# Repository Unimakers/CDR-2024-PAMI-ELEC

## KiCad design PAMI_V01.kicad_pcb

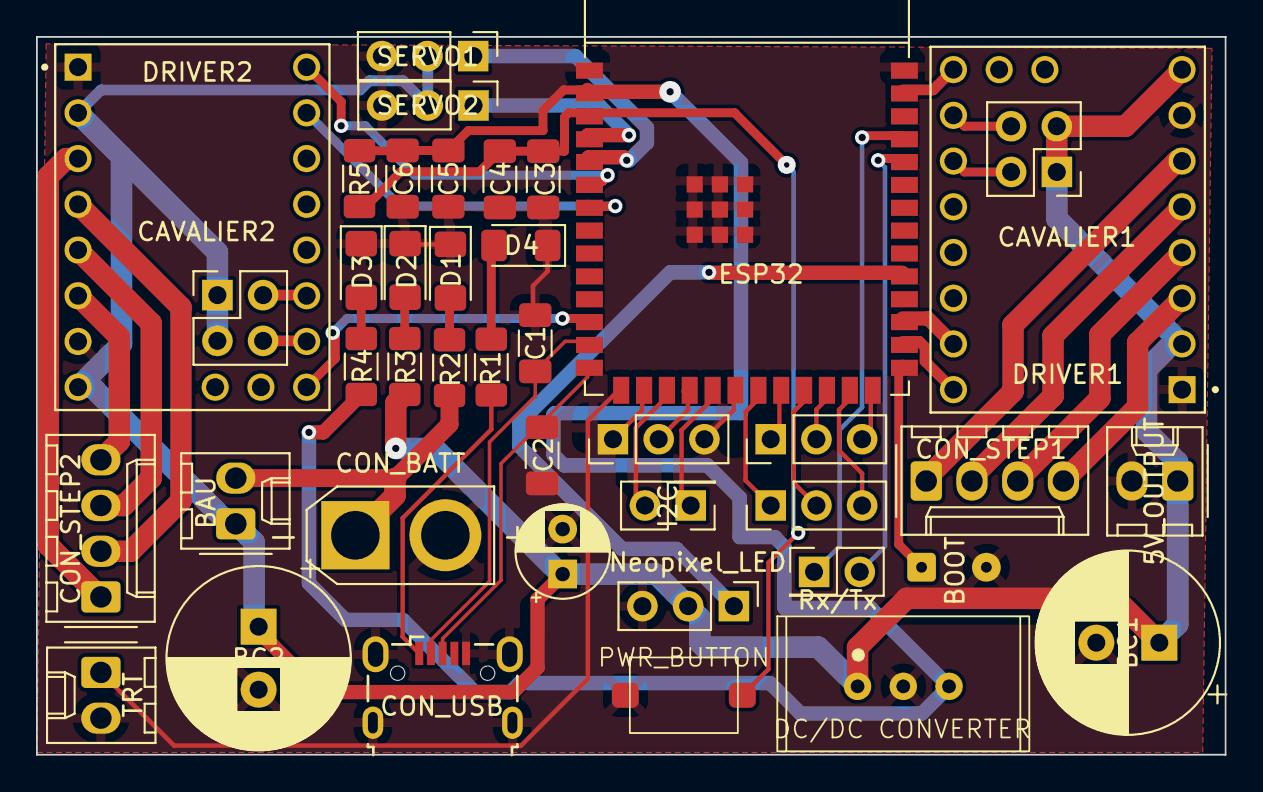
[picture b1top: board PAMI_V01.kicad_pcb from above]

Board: 2 copper layers, 66.0 x 39.9 mm, 41 parts (0 on the bottom side), 48 nets.

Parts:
5V_OUTPUT: Conn; Molex_KK-254_AE-6410-02A_1x02_P2.54mm_Vertical
BAU: BAU; Molex_KK-254_AE-6410-02A_1x02_P2.54mm_Vertical
BC1, BC2: 100uF; CP_Radial_D10.0mm_P3.50mm
BOOT: Conn; SolderWire-0.1sqmm_1x02_P3.6mm_D0.4mm_OD1mm
C1, C2, C4: TBD; C_1206_3216Metric_Pad1.33x1.80mm_HandSolder
C3, C5: 0.1uF; C_1206_3216Metric_Pad1.33x1.80mm_HandSolder
C6: 22uF; C_1206_3216Metric_Pad1.33x1.80mm_HandSolder
C7: 10uF; CP_Radial_D5.0mm_P2.50mm
CAVALIER1, CAVALIER2: Conn_02x02_Odd_Even; PinHeader_2x02_P2.54mm_Vertical
CON_BATT: Conn; AMASS_XT30U-F_1x02_P5.0mm_Vertical
CON_STEP1, CON_STEP2: Conn_01x04; Molex_KK-254_AE-6410-04A_1x04_P2.54mm_Vertical
CON_USB: USB_OTG; USB_Micro-B_Wuerth_629105150521
D1, D2, D3, D4: LED_Small; LED_1206_3216Metric_Pad1.42x1.75mm_HandSolder
DC/DC CONVERTER: TSR_2-2433; Traco 2- 24xx
DRIVER1, DRIVER2: TMC2209_SILENTSTEPSTICK; MODULE_TMC2209_SILENTSTEPSTICK
ESP32: ESP32-S3-WROOM-1
I2C: Conn_01x02; PinHeader_2x01_P2.54mm_Vertical
J7, J9, J11: Conn_01x03; PinHeader_1x03_P2.54mm_Vertical
Neopixel_LED: Neopixel_LED; PinHeader_1x03_P2.54mm_Vertical
PWR_BUTTON: SW_Push; würth WS-TASV SMT Tact Switch
R1, R2, R3, R4: R_Small; R_1206_3216Metric_Pad1.30x1.75mm_HandSolder
R5: TBD; R_1206_3216Metric_Pad1.30x1.75mm_HandSolder
Rx/Tx: Conn_01x02; PinHeader_2x01_P2.54mm_Vertical
SERVO1, SERVO2: Motor_Servo; PinHeader_1x03_P2.54mm_Vertical
TRT: TRT; Molex_KK-254_AE-6410-02A_1x02_P2.54mm_Vertical

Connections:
+3.3V: C5.2, C6.2, DC/DC CONVERTER.3 (VO), ESP32.2 (3V3), R4.2, R5.1
+5V: 5V_OUTPUT.1, BAU.1 (A), BC1.1, BC2.1, C7.1, CAVALIER1.1, CAVALIER1.3, CAVALIER2.1, CAVALIER2.3, DC/DC CONVERTER.1 (VI), DRIVER1.2 (VIO), DRIVER1.8 (VM), DRIVER2.2 (VIO), DRIVER2.8 (VM), Neopixel_LED.2 (+), R3.1, SERVO1.2 (+), SERVO2.2 (+)
+BATT: BAU.2 (B), CON_BATT.1, R2.1
/D+: C2.2, CON_USB.3 (D+), ESP32.14 (GPIO20/U1CTS/ADC2_CH9/CLK_OUT1/USB_D+)
/D-: C1.2, CON_USB.2 (D-), ESP32.13 (GPIO19/U1RTS/ADC2_CH8/CLK_OUT2/USB_D-)
GND: 5V_OUTPUT.2, BC1.2, BC2.2, BOOT.2, C1.1, C2.1, C3.1, C4.2, C5.1, C6.1, C7.2, CON_BATT.2, CON_USB.5 (GND), CON_USB.6 (Shield), D1.1 (K), D2.1 (K), D3.1 (K), D4.1 (K), DC/DC CONVERTER.2 (GND), DRIVER1.1 (GND), DRIVER1.7 (GND), DRIVER2.1 (GND), DRIVER2.7 (GND), ESP32.1 (GND), ESP32.40 (GND), ESP32.41 (GND), Neopixel_LED.3 (-), PWR_BUTTON.1, SERVO1.3 (-), SERVO2.3 (-), TRT.2 (B)
GPIO1: DRIVER1.16 (~EN), ESP32.39 (GPIO1/TOUCH1/ADC1_CH0)
GPIO4: ESP32.4 (GPIO4/TOUCH4/ADC1_CH3), SERVO2.1 (PWM)
GPIO5: ESP32.5 (GPIO5/TOUCH5/ADC1_CH4), SERVO1.1 (PWM)
GPIO6: DRIVER2.9 (DIR), ESP32.6 (GPIO6/TOUCH6/ADC1_CH5)
GPIO7: DRIVER2.10 (STEP), ESP32.7 (GPIO7/TOUCH7/ADC1_CH6)
GPIO8: DRIVER2.16 (~EN), ESP32.12 (GPIO8/TOUCH8/ADC1_CH7/SUBSPICS1)
GPIO31: ESP32.31 (GPIO38/FSPIWP/SUBSPIWP), Neopixel_LED.1 (PWM)
GPIO35: DRIVER1.9 (DIR), ESP32.28 (SPIIO6/GPIO35/FSPID/SUBSPID)
GPIO36: DRIVER1.10 (STEP), ESP32.29 (SPIIO7/GPIO36/FSPICLK/SUBSPICLK)
unnamed: D1.2 (A), R2.2
unnamed: D2.2 (A), R3.2
unnamed: D4.2 (A), R1.2
unnamed: D3.2 (A), R4.1
unnamed: CON_STEP1.1, DRIVER1.6 (M2B)
unnamed: CON_STEP1.2, DRIVER1.5 (M2A)
unnamed: CON_STEP1.3, DRIVER1.4 (M1A)
unnamed: CON_STEP1.4, DRIVER1.3 (M1B)
unnamed: CON_STEP2.1, DRIVER2.3 (M1B)
unnamed: CON_STEP2.2, DRIVER2.4 (M1A)
unnamed: CON_STEP2.3, DRIVER2.5 (M2A)
unnamed: CON_STEP2.4, DRIVER2.6 (M2B)
unnamed: BOOT.1, ESP32.27 (GPIO0/BOOT)
unnamed: CON_USB.1 (VBUS), R1.1
unnamed: CAVALIER1.2, DRIVER1.14 (MS2)
unnamed: CAVALIER1.4, DRIVER1.15 (MS1)
unnamed: CAVALIER2.2, DRIVER2.14 (MS2)
unnamed: CAVALIER2.4, DRIVER2.15 (MS1)
unnamed: ESP32.21 (GPIO13/TOUCH13/ADC2_CH2/FSPIQ/FSPIIO7/S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), J7.1
unnamed: ESP32.23 (GPIO21), J7.2
unnamed: ESP32.25 (GPIO48/SPICLK_N/SUBSPICLK_N_DIFF), J7.3
unnamed: ESP32.37 (U0TXD/GPIO43/CLK_OUT1), Rx/Tx.1
unnamed: ESP32.36 (U0RXD/GPIO44/CLK_OUT2), Rx/Tx.2
unnamed: ESP32.22 (GPIO14/TOUCH14/ADC2_CH3/FSPIWP/FSPIDQS/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), J9.1
unnamed: ESP32.24 (GPIO47/SPICLK_P/SUBSPICLK_P_DIFF), J9.2
unnamed: ESP32.26 (GPIO45), J9.3
unnamed: ESP32.19 (GPIO11/TOUCH11/ADC2_CH0/FSPID/FSPIIO5/S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), I2C.1
unnamed: ESP32.17 (GPIO9/TOUCH9/ADC1_CH8/FSPIHD/SUBSPIHD), I2C.2
unnamed: ESP32.16 (GPIO46), J11.1
unnamed: ESP32.18 (GPIO10/TOUCH10/ADC1_CH9/FSPICS0/FSPIIO4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), J11.2
unnamed: ESP32.20 (GPIO12/TOUCH12/ADC2_CH1/FSPICLK/FSPIIO6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), J11.3
unnamed: ESP32.15 (GPIO3/TOUCH3/ADC1_CH2), TRT.1 (A)
unnamed: C3.2, C4.1, ESP32.3 (EN), PWR_BUTTON.2, R5.2

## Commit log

2024-03-06 init(global : Upload board V2)
